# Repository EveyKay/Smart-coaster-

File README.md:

# Smart-coaster-
Hello! this is my smart coaster project! this is a project for week one of hack club's halflife. The goal of my smart coaster is to help people who have trouble remember to drink water, to stay hydrated. I would also like to preface the rest of this readme by saying that I have no idea what I'm doing, and this is like pretty much the first time I am using GitHub without major help. 
### What the smart coaster does-
there is pressure sensor that you place your cup on and when it senses that your cup has been on the pressure sensor too long, the little creature on the screen gets a bit more mad. as you leave your cup on the pressure sensor longer, the creature will get progressively more and more mad until it gets super mad and flashes lights and sets off a buzzer until you pick up your cup to take a sip. 
### My goal with the smart coaster- 
my goal with the smart coaster is to not only help people stay hydrated but to also learn more about PCB and the different pieces and pins of microcontroller myself
### Author
Me! EveyKay: https://github.com/EveyKay
### Files 
- BOM [`BOM.md`](BOM.md)
- PBC, Work in progress
- Final Code, Work in Progress
## Bill of Materials

Prices include each part's share of shipping and tariffs. The Mouser order totals $25.66; the OLED is a separate order. All SMD passives are 0603.

| Part | Qty | Unit | Total | Vendor | Purpose |
|---|---|---|---|---|---|
| [OLED screen (ER-OLEDM0.91-1W-I2C)](https://www.buydisplay.com/i2c-white-0-91-inch-oled-display-module-128x32-arduino-raspberry-pi) | 1 | $2.80 | $2.80 | buydisplay.com | The screen |
| [Raspberry Pi Pico (SC0915)](https://www.mouser.com/en/ProductDetail/Raspberry-Pi/SC0915?qs=T%252BzbugeAwjgnLi4azxXVFA%3D%3D) | 1 | $6.40 | $6.40 | Mouser | The brain |
| [MCP73831T-2ACI/MC](https://www.mouser.com/en/ProductDetail/Microchip-Technology/MCP73831T-2ACI-MC?qs=yUQqVecv4quJ3ICqm%2FGZxw%3D%3D) | 1 | $1.28 | $1.28 | Mouser | Battery charger |
| [JST S2B-PH-SM4-K-TB(LF)(SN)](https://www.mouser.com/en/ProductDetail/JST-Commercial/S2B-PH-SM4-K-TB-LFSN?qs=QpmGXVUTftGuZtpTcKbMuQ%3D%3D) | 1 | $0.88 | $0.88 | Mouser | Battery connector |
| [onsemi SS14 Schottky diode](https://www.mouser.com/en/ProductDetail/onsemi/SS14?qs=mVVXn4M53U%252BvrBaFv5vr4w%3D%3D) | 1 | $0.70 | $0.70 | Mouser | Power system |
| [Adafruit 166 round FSR](https://www.mouser.com/en/ProductDetail/Adafruit/166?qs=GURawfaeGuBZazGyM1uUyQ%3D%3D) | 1 | $6.32 | $6.32 | Mouser | To sense the cup |
| [Samsung CL10A475KO8NNNC (4.7uF)](https://www.mouser.com/en/ProductDetail/Samsung-Electro-Mechanics/CL10A475KO8NNNC?qs=X6jEic%2FHinAbIjmLnFfqqQ%3D%3D) | 2 | $0.32 | $0.64 | Mouser | Capacitor |
| [Wurth 61300211121 (1x2 header)](https://www.mouser.com/en/ProductDetail/Wurth-Elektronik/61300211121?qs=t4813l51qx%252B1A5GYDQxPlw%3D%3D) | 1 | $0.21 | $0.21 | Mouser | Connector pins |
| [Wurth 61302011121 (1x20 header)](https://www.mouser.com/en/ProductDetail/Wurth-Elektronik/61302011121?qs=PhR8RmCirEbj%2FFsnpbhNaw%3D%3D) | 2 | $1.955 | $3.91 | Mouser | Connector pins for the Pico |
| [Yageo RC0603FR-074K7L (4.7kOhm)](https://www.mouser.com/en/ProductDetail/YAGEO/RC0603FR-074K7L?qs=gt6vzsuosg37y0l7Vt36bQ%3D%3D) | 2 | $0.16 | $0.32 | Mouser | Pull-up resistors for the display |
| [C&K PCM12SMTR switch](https://www.mouser.com/c/?q=PCM12SMTR) | 1 | $2.05 | $2.05 | Mouser | To turn it on and off |
| [TDK PS1240P02BT buzzer](https://www.mouser.com/c/?q=PS1240P02BT) | 1 | $1.17 | $1.17 | Mouser | The buzzer |
| [LTST-C190KDKT-10A red LED](https://www.mouser.com/en/ProductDetail/LITEON/LTST-C190KDKT-10A?qs=sGAEpiMZZMt82OzCyDsLFD%252B3tm%2Fp6nZNc6zCAMVNjBI%3D) | 3 | $0.273 | $0.82 | Mouser | For the flashing lights |
| [Yageo RC0603FR-07100RL (100Ohm)](https://www.mouser.com/en/ProductDetail/YAGEO/RC0603FR-07100RL?qs=NEN%2FsE%2FLsvPIwIWKCOS4%2FA%3D%3D) | 2 | $0.16 | $0.32 | Mouser | Resistor |
| [Panasonic ERJ-3EKF1001V (1kOhm)](https://www.mouser.com/en/ProductDetail/Panasonic-Industry/ERJ-3EKF1001V?qs=H7k1u0Mp9JTM8yQxOuvoDg%3D%3D) | 3 | $0.16 | $0.48 | Mouser | LED resistance |
| [Yageo RC0603FR-0710KL (10kOhm)](https://www.mouser.com/en/ProductDetail/YAGEO/RC0603FR-0710KL?qs=grNVn54RoB%252B3GtjbJj3wJQ%3D%3D) | 1 | $0.16 | $0.16 | Mouser | Resistor |

**Total: $28.46** ($25.66 from Mouser + $2.80 OLED from buydisplay.com)
## code 
Here is the most current version of code, it is still very much a prototype right now, it doesn't actually work for the board that I made because it was for a prototype: [`tinker_cad_prototype_code1.ino`](tinker_cad_prototype_code1.ino)

## Pcb 
Here is the pictures of the Pcb that I Made and the schematic: 

- And here is the ki cad file for the pcb I Made: Eveys Engineering project.kicad_pcb
- all the other files like the drill files and the schematic file are all also in the repository 
- I made my PCB in kicad

## History
### Tinkercad Prototype 
Im am not that good at electronics ... Yet. so because of my lack of experience I decided to make a digital prototype through tinkercad so I could mess around with pins on the micro controller and  practice coding. here is a picture of v1 of the smart coaster and the code I make in tinker cad, neither of these will be used in the final version. 

```py
// C++ code
//
#include <Adafruit_LiquidCrystal.h>

int ok = 0;

Adafruit_LiquidCrystal lcd_2(2);

void setup()
{
  pinMode(LED_BUILTIN, OUTPUT);
  pinMode(A0, INPUT);
  Serial.begin(9600);
  lcd_2.begin(16, 2);
  pinMode(9, OUTPUT);
  pinMode(8, OUTPUT);
  pinMode(7, OUTPUT);
  pinMode(2, OUTPUT);
}

void loop()
{
  digitalWrite(LED_BUILTIN, HIGH);
  delay(1000); // Wait for 1000 millisecond(s)
  digitalWrite(LED_BUILTIN, LOW);
  delay(1000); // Wait for 1000 millisecond(s)

  if (analogRead(A0) < 1017) {
    Serial.println("Good job!");
  }

  if (analogRead(A0) > 1017) {
    delay(1000); // Wait for 1000 millisecond(s)
    Serial.println("water?");
    lcd_2.print("Water?");
    delay(1000); // Wait for 1000 millisecond(s)
    Serial.println("Water!");
    lcd_2.print("Water!");
    delay(1000); // Wait for 1000 millisecond(s)
    Serial.println("WATERRRR!");
    lcd_2.print("WATEERRRRR!!!!");
    while (analogRead(A0) > 1017) {
      digitalWrite(9, HIGH);
      digitalWrite(8, HIGH);
      digitalWrite(7, HIGH);
      digitalWrite(2, HIGH);
      delay(100); // Wait for 100 millisecond(s)
      digitalWrite(9, LOW);
      digitalWrite(8, LOW)
      ;digitalWrite(7, LOW);
      digitalWrite(2, LOW);
      delay(100); // Wait for 100 millisecond(s)
      digitalWrite(9, HIGH);
      digitalWrite(8, HIGH);
      digitalWrite(7, HIGH);
      digitalWrite(2, HIGH);
      delay(100); // Wait for 100 millisecond(s)
      digitalWrite(9, LOW);
      digitalWrite(8, LOW);
      digitalWrite(7, LOW);
      digitalWrite(2, LOW);
    }
  }
}
```

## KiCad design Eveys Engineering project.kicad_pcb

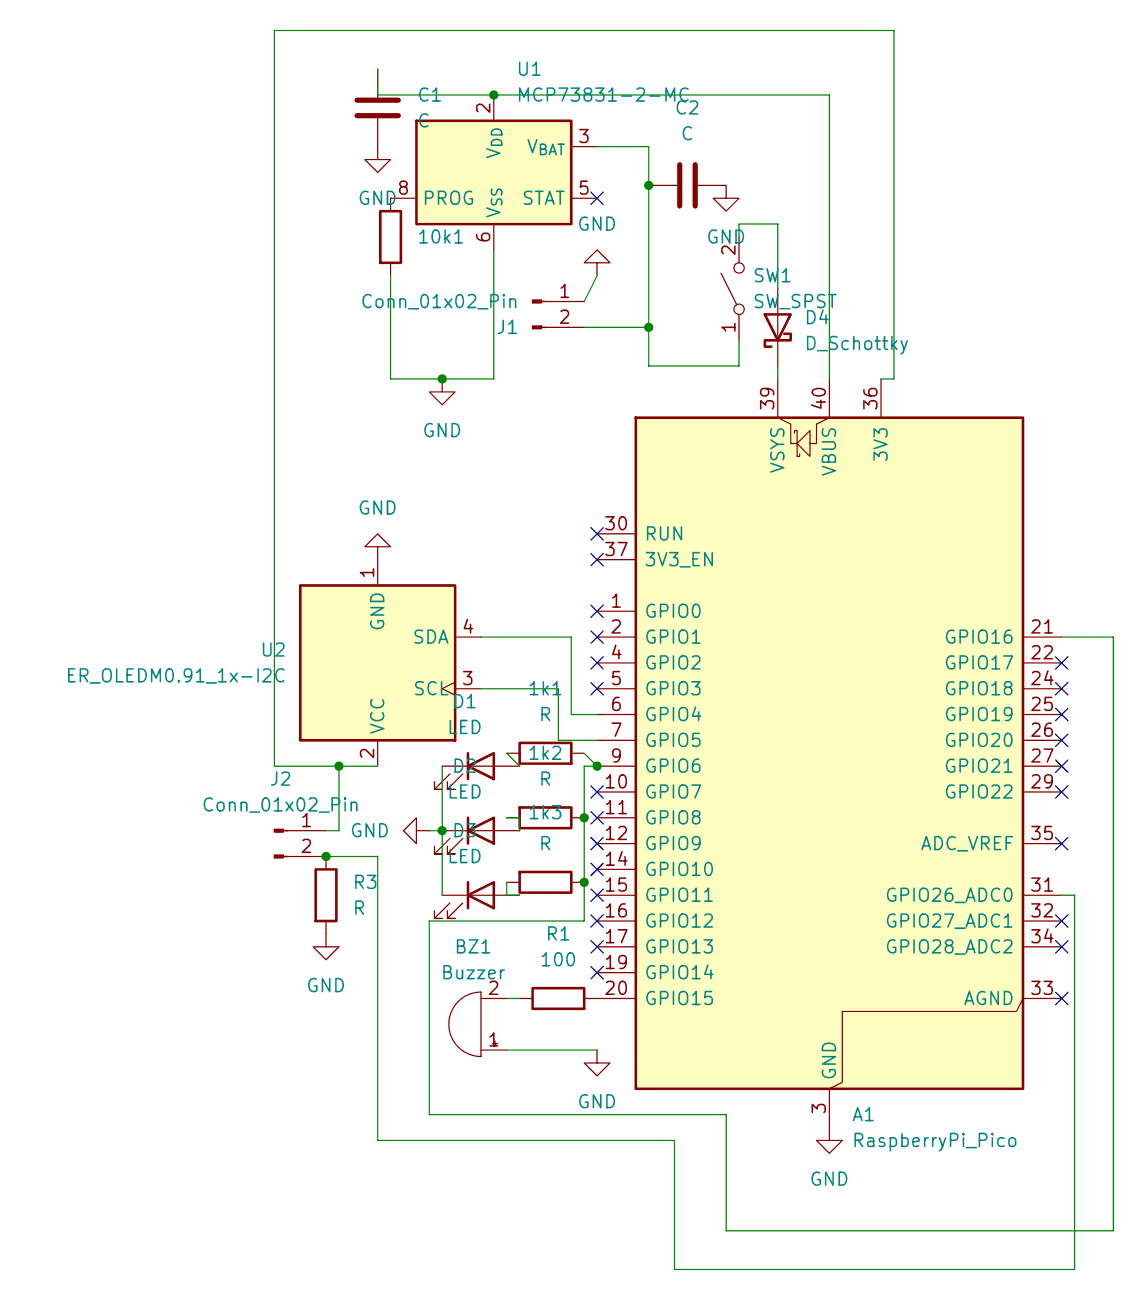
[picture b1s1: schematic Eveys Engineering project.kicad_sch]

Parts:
1k1, 1k2, 1k3, 10k1: R; R_0805_2012Metric
A1: RaspberryPi_Pico; RaspberryPi_Pico_Common_Unspecified
BZ1: Buzzer; Buzzer_12x9.5RM7.6
C1, C2: C; C_0805_2012Metric
D1, D2, D3: LED; LED_0805_2012Metric
D4: D_Schottky; D_SMA
J1: Conn_01x02_Pin; JST_PH_B2B-PH-SM4-TB_1x02-1MP_P2.00mm_Vertical
J2: Conn_01x02_Pin; PinSocket_1x02_P2.54mm_Vertical
R1: 100; R_0805_2012Metric
R3: R; R_0805_2012Metric
SW1: SW_SPST; SW_SPDT_PCM12
U1: MCP73831-2-MC; DFN-8-1EP_3x2mm_P0.5mm_EP1.7x1.4mm
U2: ER_OLEDM0.91_1x-I2C

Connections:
GND: 10k1.2, A1.3 (GND), A1.8 (GND), A1.13 (GND), A1.18 (GND), A1.23 (GND), A1.28 (GND), A1.38 (GND), BZ1.1 (+), C1.2, C2.1, D1.1 (K), D2.1 (K), D3.1 (K), J1.1, R3.2, U1.6 (V_{SS}), U2.1 (GND)
unnamed: A1.36 (3V3), J2.1, U2.2 (VCC)
unnamed: A1.6 (GPIO4), U2.4 (SDA)
unnamed: A1.7 (GPIO5), U2.3 (SCL)
unnamed: A1.20 (GPIO15), R1.2
unnamed: 1k1.2, 1k2.1, 1k3.1, A1.9 (GPIO6), A1.21 (GPIO16)
unnamed: A1.31 (GPIO26_ADC0), J2.2, R3.1
unnamed: A1.40 (VBUS), C1.1, U1.1 (V_{DD}), U1.2 (V_{DD})
unnamed: A1.39 (VSYS), D4.1 (K)
unnamed: BZ1.2 (-), R1.1
unnamed: 1k1.1, D1.2 (A)
unnamed: 1k2.2, D2.2 (A)
unnamed: 1k3.2, D3.2 (A)
unnamed: D4.2 (A), SW1.2 (B)
unnamed: C2.2, J1.2, SW1.1 (A), U1.3 (V_{BAT}), U1.4 (V_{BAT})
unnamed: 10k1.1, U1.8 (PROG)

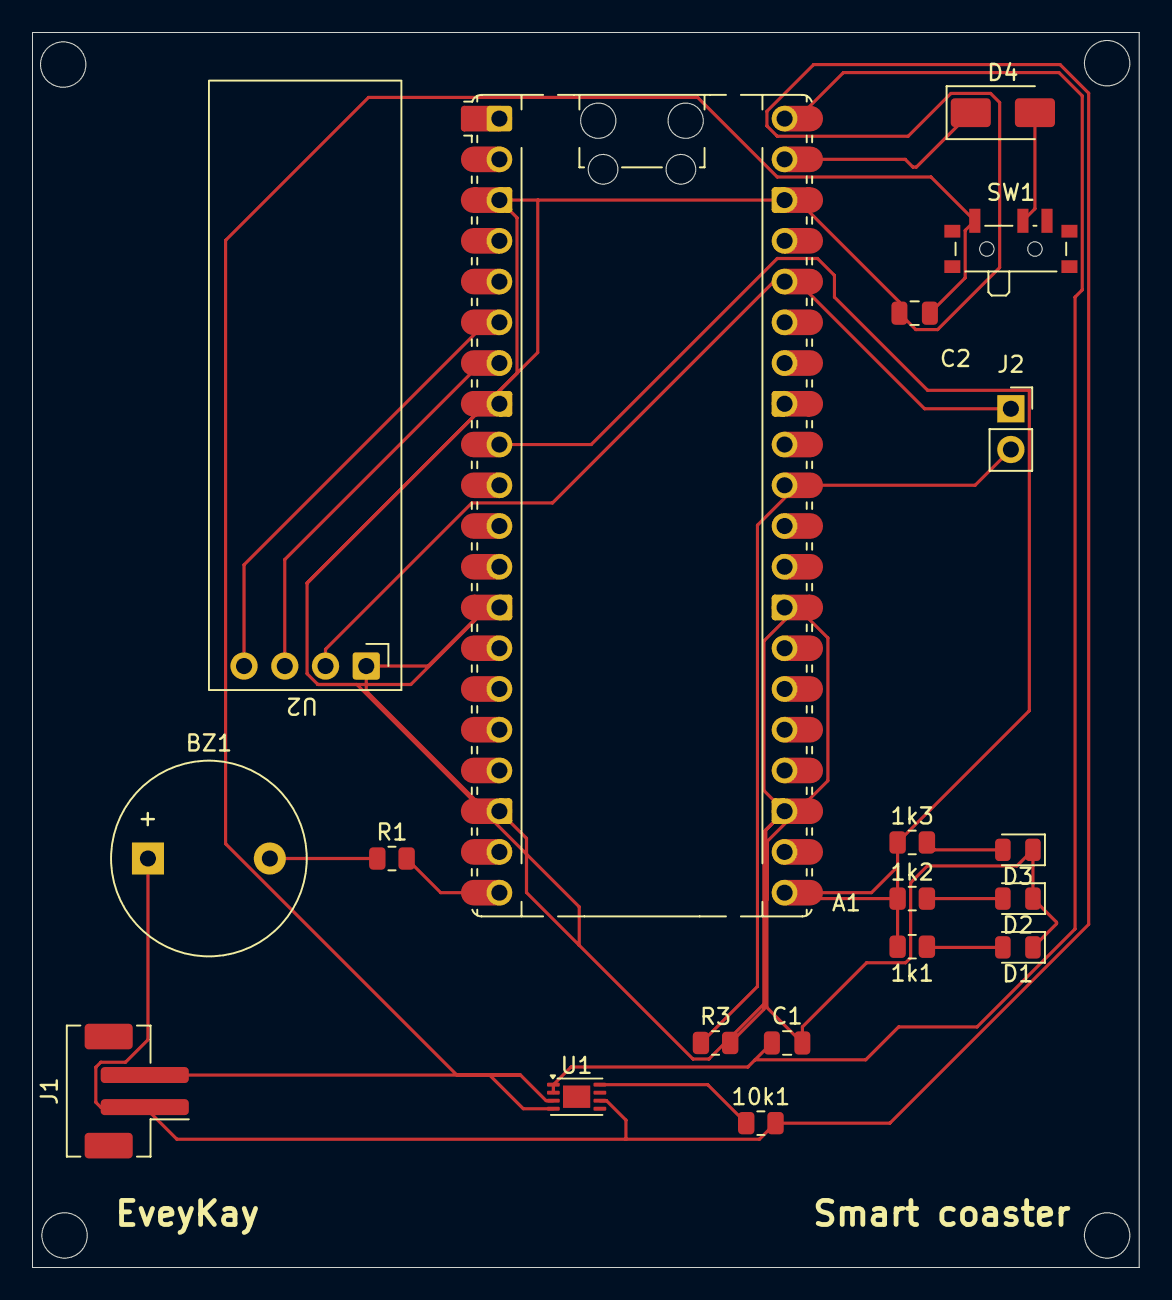
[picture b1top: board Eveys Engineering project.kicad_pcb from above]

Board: 2 copper layers, 69.0 x 77.0 mm, 19 parts (0 on the bottom side), 16 nets.
